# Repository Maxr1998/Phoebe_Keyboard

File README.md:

# Phoebe Keyboard

CAD files for case, plate and PCB of my Phoebe Mechanical Keyboard.

## License

All files in the repository are licensed under a [Creative Commons Attribution-ShareAlike 4.0 International License](http://creativecommons.org/licenses/by-sa/4.0/).

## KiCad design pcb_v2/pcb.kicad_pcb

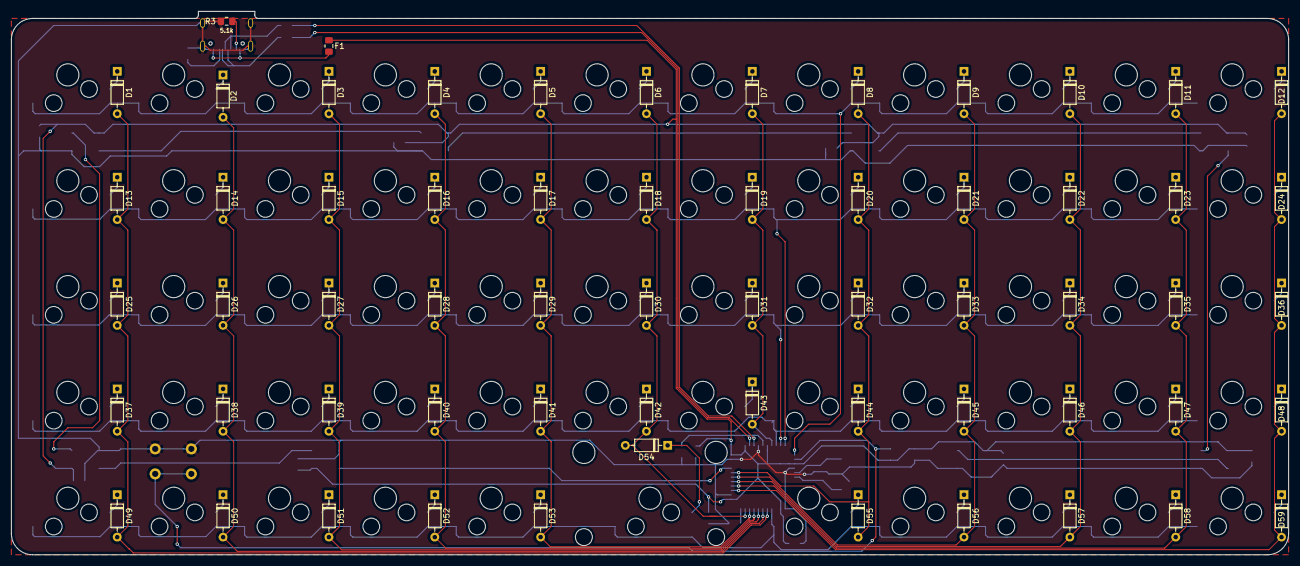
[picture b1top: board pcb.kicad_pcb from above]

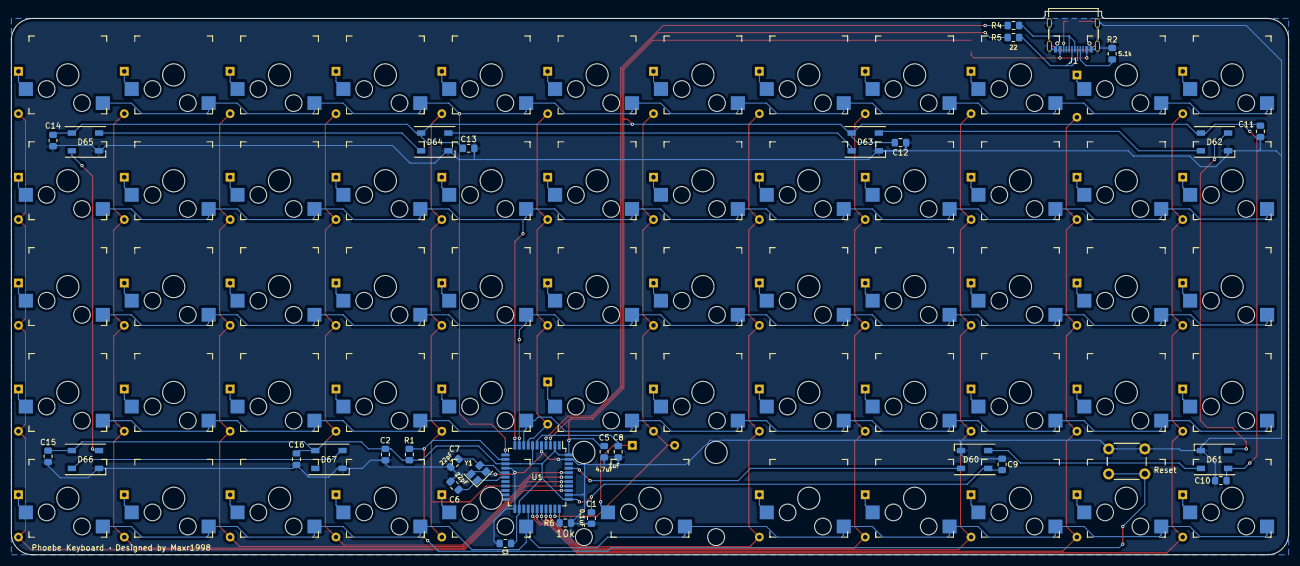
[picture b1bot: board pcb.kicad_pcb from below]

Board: 2 copper layers, 229.9 x 97.8 mm, 152 parts (32 on the bottom side), 98 nets.

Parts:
C1, C2, C3: 0.1uF; C_0805_2012Metric_Pad1.15x1.40mm_HandSolder
C5: 4.7uF; C_0805_2012Metric_Pad1.15x1.40mm_HandSolder
C6, C7: 22pF; C_0805_2012Metric_Pad1.15x1.40mm_HandSolder
C8: 1uF; C_0805_2012Metric_Pad1.15x1.40mm_HandSolder
C9, C10, C11, C12, C13, C14, C15, C16: 100nF; C_0805_2012Metric_Pad1.15x1.40mm_HandSolder
D1, D2, D3, D4, D5, D6, D7, D8, D9, D10, D11, D12, D13, D14, D15, D16, D17, D18, D19, D20, D21, D22, D23, D24, D25, D26, D27, D28, D29, D30, D31, D32, D33, D34, D35, D36, D37, D38, D39, D40, D41, D42, D43, D44, D45, D46, D47, D48, D49, D50, D51, D52, D53, D54, D55, D56, D57, D58, D59: 1N4148; D_DO-35_SOD27_P7.62mm_Horizontal
D60, D61, D62, D63, D64, D65, D66, D67: WS2812B; LED_WS2812B_PLCC4_5.0x5.0mm_P3.2mm
F1: 500mA; Fuse_0805_2012Metric_Pad1.15x1.40mm_HandSolder
J1: USB_C_Receptacle_USB2.0; USB_C_Receptacle_Palconn_UTC16-G
R1, R6: 10k; R_0805_2012Metric_Pad1.15x1.40mm_HandSolder
R2, R3: 5.1k; R_0805_2012Metric_Pad1.15x1.40mm_HandSolder
R4, R5: 22; R_0805_2012Metric_Pad1.15x1.40mm_HandSolder
SW1: Reset; SW_PUSH_6mm
SW2, SW3, SW4, SW5, SW6, SW7, SW8, SW9, SW10, SW11, SW12, SW13, SW14, SW15, SW16, SW17, SW18, SW19, SW20, SW21, SW22, SW23, SW24, SW25, SW26, SW27, SW28, SW29, SW30, SW31, SW32, SW33, SW34, SW35, SW36, SW37, SW38, SW39, SW40, SW41, SW42, SW43, SW44, SW45, SW46, SW47, SW48, SW49, SW50, SW51, SW52, SW53, SW54, SW55, SW56, SW57, SW58, SW59, SW60: SW_Push; Kailh_socket_plate_mount
U1: ATmega32U4-AU; TQFP-44_10x10mm_P0.8mm
Y1: TSX3225; Crystal_SMD_SeikoEpson_TSX3225-4Pin_3.2x2.5mm

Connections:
/CH_EN: R6.2, U1.33
/RESET: R1.1, SW1.2, U1.13
/XTAL_N: C7.1, U1.16, Y1.3
/XTAL_P: C6.2, U1.17, Y1.1
GND: C1.2, C2.2, C3.2, C5.2, C6.1, C7.2, C8.2, C9.2, C10.2, C11.2, C12.2, C13.2, C14.2, C15.2, C16.2, D60.3, D61.3, D62.3, D63.3, D64.3, D65.3, D66.3, D67.3, J1.A1, J1.A12, J1.B1, J1.B12, J1.S1, R2.1, R3.1, R6.1, SW1.1, U1.5, U1.15, U1.23, U1.35, U1.43, Y1.2, Y1.4
unnamed: C8.1, U1.6
unnamed: D1.1, SW2.2
unnamed: D2.1, SW3.2
unnamed: D3.1, SW4.2
unnamed: D4.1, SW5.2
unnamed: D5.1, SW6.2
unnamed: D6.1, SW7.2
unnamed: D7.1, SW8.2
unnamed: D8.1, SW9.2
unnamed: D9.1, SW10.2
unnamed: D10.1, SW11.2
unnamed: D11.1, SW12.2
unnamed: D12.1, SW13.2
unnamed: D13.1, SW14.2
unnamed: D14.1, SW15.2
unnamed: D15.1, SW16.2
unnamed: D16.1, SW17.2
unnamed: D17.1, SW18.2
unnamed: D18.1, SW19.2
unnamed: D19.1, SW20.2
unnamed: D20.1, SW21.2
unnamed: D21.1, SW22.2
unnamed: D22.1, SW23.2
unnamed: D23.1, SW24.2
unnamed: D24.1, SW25.2
unnamed: D25.1, SW26.2
unnamed: D26.1, SW27.2
unnamed: D27.1, SW28.2
unnamed: D28.1, SW29.2
unnamed: D29.1, SW30.2
unnamed: D30.1, SW31.2
unnamed: D31.1, SW32.2
unnamed: D32.1, SW33.2
unnamed: D33.1, SW34.2
unnamed: D34.1, SW35.2
unnamed: D35.1, SW36.2
unnamed: D36.1, SW37.2
unnamed: D37.1, SW38.2
unnamed: D38.1, SW39.2
unnamed: D39.1, SW40.2
unnamed: D40.1, SW41.2
unnamed: D41.1, SW42.2
unnamed: D42.1, SW43.2
unnamed: D43.1, SW44.2
unnamed: D44.1, SW45.2
unnamed: D45.1, SW46.2
unnamed: D46.1, SW47.2
unnamed: D47.1, SW48.2
unnamed: D48.1, SW49.2
unnamed: D49.1, SW50.2
unnamed: D50.1, SW51.2
unnamed: D51.1, SW52.2
unnamed: D52.1, SW53.2
unnamed: D53.1, SW54.2
unnamed: D54.1, SW55.2
unnamed: D55.1, SW56.2
unnamed: D56.1, SW57.2
unnamed: D57.1, SW58.2
unnamed: D58.1, SW59.2
unnamed: D59.1, SW60.2
unnamed: D60.2, D61.4
unnamed: D61.2, D62.4
unnamed: D62.2, D63.4
unnamed: D63.2, D64.4
unnamed: D64.2, D65.4
unnamed: D65.2, D66.4
unnamed: D66.2, D67.4
unnamed: J1.A5, R2.2
unnamed: J1.A6, J1.B6, R4.2
unnamed: J1.A7, J1.B7, R5.2
unnamed: J1.B5, R3.2
unnamed: R4.1, U1.4
unnamed: R5.1, U1.3
VBUS: F1.2, J1.A4, J1.A9, J1.B4, J1.B9
VCC: C1.1, C2.1, C3.1, C5.1, C9.1, C10.1, C11.1, C12.1, C13.1, C14.1, C15.1, C16.1, D60.1, D61.1, D62.1, D63.1, D64.1, D65.1, D66.1, D67.1, F1.1, R1.2, U1.2, U1.7, U1.14, U1.24, U1.34, U1.44
col0: D1.2, D13.2, D25.2, D37.2, D49.2, U1.27
col1: D2.2, D14.2, D26.2, D38.2, D50.2, U1.28
col2: D3.2, D15.2, D27.2, D39.2, D51.2, U1.29
col3: D4.2, D16.2, D28.2, D40.2, D52.2, U1.30
col4: D5.2, D17.2, D29.2, D41.2, D53.2, U1.31
col5: D6.2, D18.2, D30.2, D42.2, D54.2, U1.32
col6: D7.2, D19.2, D31.2, D43.2, U1.8
col7: D8.2, D20.2, D32.2, D44.2, D55.2, U1.40
col8: D9.2, D21.2, D33.2, D45.2, D56.2, U1.39
col9: D10.2, D22.2, D34.2, D46.2, D57.2, U1.38
col10: D11.2, D23.2, D35.2, D47.2, D58.2, U1.37
col11: D12.2, D24.2, D36.2, D48.2, D59.2, U1.36
led0: D60.4, U1.41
row0: SW2.1, SW3.1, SW4.1, SW5.1, SW6.1, SW7.1, SW8.1, SW9.1, SW10.1, SW11.1, SW12.1, SW13.1, U1.12
row1: SW14.1, SW15.1, SW16.1, SW17.1, SW18.1, SW19.1, SW20.1, SW21.1, SW22.1, SW23.1, SW24.1, SW25.1, U1.11
row2: SW26.1, SW27.1, SW28.1, SW29.1, SW30.1, SW31.1, SW32.1, SW33.1, SW34.1, SW35.1, SW36.1, SW37.1, U1.10
row3: SW38.1, SW39.1, SW40.1, SW41.1, SW42.1, SW43.1, SW44.1, SW45.1, SW46.1, SW47.1, SW48.1, SW49.1, U1.9
row4: SW50.1, SW51.1, SW52.1, SW53.1, SW54.1, SW55.1, SW56.1, SW57.1, SW58.1, SW59.1, SW60.1, U1.26

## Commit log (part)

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2019-04-21 Initial
2019-04-21 Add bottom plate
2019-04-22 Add PCB design
2019-04-22 Add README
2019-04-22 Add a fuse between VBUS and VCC
2019-04-22 Add decoupling capacitors for LEDs
2019-04-22 Export settings
2019-04-22 Add Gerber files
2019-04-22 Add distance measurement for spacebar switch
2019-04-23 Add name and author to PCB
2019-05-02 Add infill, reroute col11
2019-05-02 Update gerber files
2019-05-02 Remove switch labels
2019-05-24 Add mid-layer dxf
2019-07-12 Add some dimension markers
2019-07-12 Update case scheme
    Add cutout for USB port
2019-12-04 Rework PCB design
    New USB plug, better placement of capacitors, different footprint for crystal
2019-12-04 Remove unecessary files
2024-12-09 Upgrade to latest KiCAD and tweak measurements
